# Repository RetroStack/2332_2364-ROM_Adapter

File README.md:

# 2332/2364 ROM Adapter

This repository provides an adapter for 2332 and 2364 ROMs for vintage computers. With an optional hidden inverter chip on the bottom, all versions of these boards can be emulated. The adapter was designed to have the smallest possible footprint while still using through-hole components for a vintage look. It includes an optional detachable selector board for DIP switches or jumpers. Without the detachable selector board, solder jumpers can be used instead. The provided pads on the bottom allow for synchronized address selection across multiple adapters. The entire project is available under the MIT license.

## Project Details

### Latest Files

In the "Latest" folder, you'll find the most up-to-date design files, including:

- Gerber files suitable for popular online PCB manufacturers like [PCBWay](/Latest/2332_2364_ROM_Adapter_Gerber_PCBWay.zip) and [JLCPCB](/Latest/2332_2364_ROM_Adapter_Gerber_JLCPCB.zip). Most manufacturers should be fine with either.
- A Bill of Materials (BOM) in both [CSV](/Latest/2332_2364_ROM_Adapter_BOM.csv) (with sources) and [PDF](/Latest/2332_2364_ROM_Adapter_BOM.pdf) formats.
- The [full schematics](/Latest/2332_2364_ROM_Adapter_Schematics.pdf) of the adapter.

### Implementation

The adapter has been implemented using KiCAD 7. The KiCAD project files are included in this repository.

### Assembly Instructions

1. Get a straight male pin header with pitch (2.54mm; standard) and break it to a 12-pin length. Do this twice. A machined header is recommended if the adapter will be inserted into a socket. Inserting a square pin in a socket might damage it.
2. Solder the pins in place into the smaller 12-pin lengthwise holes. To align them correctly, you can use another socket or a breadboard. Stick the longer parts into the socket/breadboard and put the PCB on top. Solder first both edges on each. Recheck if they are flush to the header. If not, reheat the corner that needs correction and press down on PCB until flush. Then, solder all other pins.
3. Install the resistor network. One edge has a square around one pin. This should be where pin 1 will be inserted. Pin 1 is identified on the resistor network usually with a dot.
4. Write/burn one of the binaries onto a ROM.
5. (Optional) Solder a socket in place. Similarly to the headers mentioned above, only solder one pin on each side before soldering all to be able to make adjustments as needed. Adding a socket is not recommended for machines which do not have enough clearance for it (e.g., TRS-80 Model 1). For these, you need to skip this step and solder the ROM directly to the board.
6. Solder the ROM to the board or insert it into the socket. Since the pins are close, this might be tricky.

#### Bank Switching

The adapter allows for bank-switching of various ROMs. Depending on the size of the ROM used, only certain pins may be configurable. For example, a 27256 ROM has 15 address pins. The adapter exposes 13 of these pins to the bottom pins, leaving 2 additional address lines available for bank-switching. A 27512 would then have 3 additional address lines.

**NOTE**: Keep in mind that the bits are active-low. This means that if you want to set a `1` on a specific address, you leave it unbridged. If you want a `0`, you should bridge it. See below for more details on why it was designed this way.

**NOTE**: The board exposes the bits from right to left. If you prefer left to right (e.g., for DIP switches to match labels), you can flip the address bits in the ROM or use the provided "f" versions in the systems ROM repository.

Here are some examples of available bank-switching configurations:

#### No Bank-Switching at all

7. Clip off extension board on perforated line.
8. Use solder bridges on the bottom to pre-select a specific ROM.

#### Jumper Caps

7. Add a 2-row pin straight header (2.54mm pitch) to the center two pins of the extension board. Make sure to leave one row of pins on each side—one row on the edge and one next to the ROM.
8. Add jumpers.

#### Right Angle Jumpers

7) Clip off extension board on perforated line.
8) Add a 2 row pin right-angle header (2.54mm pitch) to the bottom of the PCB, extending one end out over the board where the extension was.
9) Add jumpers.

#### DIP Switches

**NOTE**: For the TRS-80 Model 1, use low-profile DIP switches to ensure the adapter fits inside the case.
7) Add a DIP switch to the extension board. The DIP switch should cover all holes from front to back.

#### DIP Switches on extension board

7) Clip off the extension board along the perforated line.
8) Solder up to 6 wires (e.g., ribbon cable) to the bottom of the PCB. Use up to 3 wires for each address line, which is the row close to the center of the board. To identify the address lines, refer to the label just below the ROM on the top of the adapter PCB. Solder at least one wire to any of the holes closer to the edge of the board—these are ground pins, so any of them can be used.
9) Solder all wires to the extension board using the central two rows of holes. Solder from the bottom, as the DIP switches will be added to the top. Solder the address lines closest to the perforated line where the extension board was attached to the adapter PCB. Solder the ground wires to the other holes in the second row, further from the perforated edge.
10) Add a DIP switch to the extension board. The DIP switch should cover all holes from front to back. You may need to trim the soldered pins of the cable to allow the DIP switches to sit as close to flush as possible.

#### Jumper caps on extension board

7) Clip off the extension board along the perforated line.  
8) Solder up to 6 wires (e.g., ribbon cable) to the bottom of the PCB. Use up to 3 wires for each address line, which is the row close to the center of the board. To identify which address line is which, refer to the label just below the ROM on the top of the adapter PCB. Solder at least one wire to any of the holes closer to the edge of the board—these are ground pins, so any of them can be used.  
9) Add a 2-row pin straight header (2.54mm pitch) to the center two pins of the extension board. Leave one row on each side—one on the edge and one next to the ROM.  
10) Solder all wires to the extension board. Solder the address lines to the row closer to the perforated edge, and solder the single ground wire to the hole at the bottom edge furthest from the perforated edge. You can solder this from either the top or bottom.  
11) Add jumpers.

#### Connect two or more adapters together

Sometimes it is useful to be able to bank-switch multiple ROMs simultaneously.

7) Clip off the extension boards on nearly all the boards at the perforated line—except one, which will be used for selection.  
8) Solder up to 6 wires (e.g., ribbon cable) to the bottom of one PCB. Use up to 3 wires for each address line, which is the row close to the center of the board. To identify which address line is which, refer to the label just below the ROM on the top of the adapter PCB. Solder at least one wire to any of the holes closer to the edge of the board—these are ground pins, so any of them can be used.  
9) Repeat the same process for the other board using the other end of the wires. Ensure that the wires from each pad on one adapter connect to the corresponding pad on the other adapter.

### Configuration

Depending on which ROM and even the specific version you want to emulate, you will need to configure the adapter accordingly. Below is a list of configurations:

#### 2332 (with pin 20 as "active low")
- Switch jumper JP4: 1) Cut one side, 2) solder the other
- Connect JP8 to either 5V or GND, depending on the value you want for address line A12 (starting from A0).
- Cut jumper JP6

#### 2332 (with pin 20 as "active high")
- Install U3 (74LS04)
- Switch jumper JP7: 1) Cut one side, 2) solder the other

#### 2332 (with pin 21 as "active low")
- This is the default. Nothing else to do.

#### 2332 (with pin 21 as "active high")
- Install U3 (74LS04)
- Switch jumper JP5: 1) Cut one side, 2) solder the other

#### 2364 (with pin 20 as "active low")

This is the default configuration. No additional steps are required.

#### 2364 (with pin 20 as "active high")
- Install U3 (74LS04)
- Switch jumper JP7: 1) Cut one side, 2) solder the other

### Q&A

#### Why is the configuration active low?

Some ROMs, especially EEPROMs, have an active-low WRITE pin that needs to be HIGH (or `1`) during normal (read) use. To prevent accidentally putting ROMs into the incorrect mode (write mode instead of read mode), all additional pins are pulled high by default through pull-up resistors.

#### Why are address lines from right to left?

Having them in this orientation was the simplest solution without adding complexity to the design. Additionally, the addressing depends on the type of configuration you use. Binary numbers are typically written from right to left (as implemented), which works best for jumpers, for example. However, DIP switches use labels from left to right.

Overall, one direction had to be chosen, and I opted for the simplest. This can be adjusted by flipping the address bits. ROMs with this fix are already marked with an "f".

### Bill of Materials (BOM)

Below is a list of materials needed to assemble a complete system. Please note that the links and prices (scroll to the right to see them; as of August 22nd, 2024) will not be updated in the future and should only be used as a reference for locating the correct items.

**NOTE**: Links and alternatives are provided to assist you in finding the necessary components. I cannot guarantee the complete accuracy or reliability of all these links and alternatives. Please verify the information for yourself.

| PCB REFERENCE | QTY | VALUE       | COMMENT                                                                                                                                                                                                                          | EACH | TOTAL | SOURCE LINK                                                                               |
| ------------- | --- | ----------- | -------------------------------------------------------------------------------------------------------------------------------------------------------------------------------------------------------------------------------- | ---- | ----- | ----------------------------------------------------------------------------------------- |
| RN1           | 1   | 4.7k Ohm    | 3 resistor network with 4-pins, bussed resistors                                                                                                                                                                                 | 0.35  | 0.35   | [Mouser](https://www.mouser.com/ProductDetail/652-4604X-1LF-4.7K)                         |
| U1            | 2   |             | Source Link is for a rather expensive version of a machined straight male pin header with 40-pins which can be broken into smaller pieces to server for both. There are cheaper ones, but the link is used for future reference. | 1.0  | 1.0   | [Mouser](https://www.amazon.com/ZYAMY-2-54mm-Breakable-Straight-Connector/dp/B0778KCHHR/) |
| U2            | 1   | 2x64-2x512  | Examples are 23128, 23256, 2764, 27128, 27256, 27512, 2864, 28256 and all other variations such as 27C256 or AT28C64B                                                                                                            | 5.5  | 5.5   | [Mouser](https://www.mouser.com/ProductDetail/556-AT28C64B15PU)                           |
| U3            | 1   | 74LS04  | Optional. Needed for inverting chip select pins. | 0.68  | 0.68   | [Mouser](https://www.mouser.com/ProductDetail/595-SN74LS04D)                           |
| J1            | 1   | -           | Optional. Could be used for right-angle jumpers or attaching ribbon cable to move switch towards more accessible place.                                                                                                          | 1.02 | 1.02  | [Mouser](https://www.mouser.com/ProductDetail/649-1012938294001BLF)                       |
| J2            | 1   | -           | Optional. Adding the ability to switch character sets.                                                                                                                                                                           | 0.27 | 0.27  | [Mouser](https://www.mouser.com/ProductDetail/571-1033222)                                |
|               | 1   | Low-profile | Optional. Adding the ability to switch character sets.                                                                                                                                                                           | 0.67 | 0.67  | [Mouser](https://www.mouser.com/ProductDetail/774-2105MS)                                 |

### ROM Binaries

This repository contains only the adapter boards. The ROM binaries themselves can be found in other repositories and sources. Below is a list of known binary sources:

- [TRS-80 Model 1](https://github.com/RetroStack/TRS-80-Model-I-System-ROMs) - RetroStack

More sources will be added over time. Let me know if you are aware of good sources.

### RetroStack Libraries

To work with this KiCAD project, you'll need the RetroStack libraries for KiCAD. Please [follow this link](https://www.github.com/RetroStack/KiCAD-Libraries) to access and install these libraries.

## Support this Project

RetroStack is passionate about exploring and preserving the legacy of older computer systems. My work involves creating detailed documentation and videos to share the knowledge. I am also dedicated to reviving these classic systems by reimplementing them and offering replacement parts at no cost. If you're keen on supporting this unique project, I invite you to visit my [Patreon page](https://www.patreon.com/RetroStack). Your support would be immensely valuable and greatly appreciated!

## License

This project is licensed under the MIT License - see the [LICENSE](LICENSE) file for details.

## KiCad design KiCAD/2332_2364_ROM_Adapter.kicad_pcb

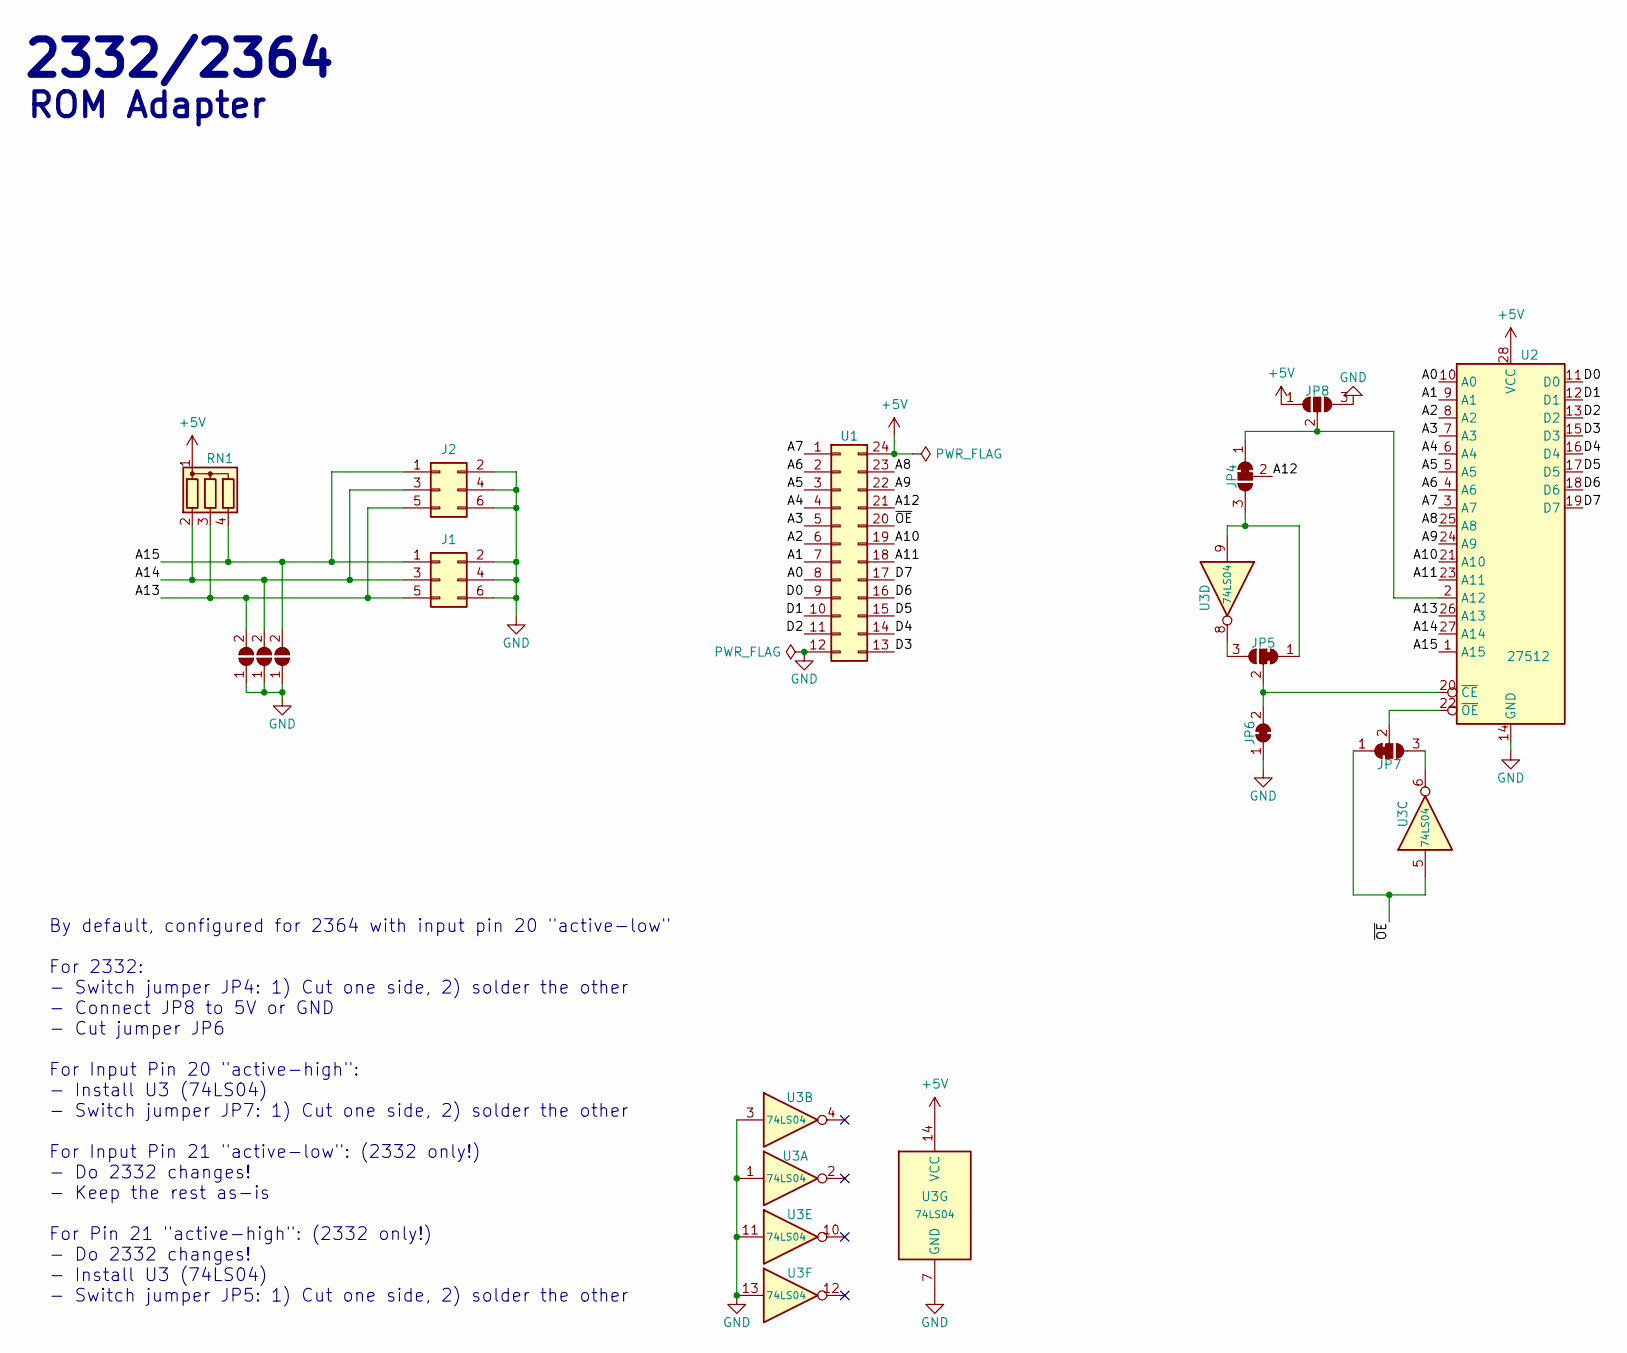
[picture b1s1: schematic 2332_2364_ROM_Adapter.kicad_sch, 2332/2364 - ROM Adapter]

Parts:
J1: Conn_02x03_Odd_Even; DIPJumper_3
J2: Conn_02x03_Odd_Even; PinHeader_2x03_P2.54mm_Vertical
JP1, JP2, JP3: SolderJumper_2_Open; SolderJumper_2_Open_RoundedPad
JP4, JP5, JP7: Switch for 2332!; SolderJumper-3_P1.3mm_Bridged12_RoundedPad1.0x1.5mm_NumberL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
JP6: SolderJumper_2_Bridged; SolderJumper-2_P1.3mm_Bridged_RoundedPad1.0x1.5mm
JP8: SolderJumper_3_Open; SolderJumper-3_P1.3mm_Open_RoundedPad1.0x1.5mm_NumberLabels
RN1: R_Network03; R_Array_SIP4
U1: Conn_02x12_Counter_Clockwise; DIP-24_W15.24mm
U2: 27512; DIP-28_W15.24mm
U3: 74LS04; SOIC-14_3.9x8.7mm_P1.27mm

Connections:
+5V: JP8.1 (A), RN1.1 (common), U1.24, U2.28 (VCC), U3.14 (VCC)
/A0: U1.8, U2.10 (A0)
/A1: U1.7, U2.9 (A1)
/A2: U1.6, U2.8 (A2)
/A3: U1.5, U2.7 (A3)
/A4: U1.4, U2.6 (A4)
/A5: U1.3, U2.5 (A5)
/A6: U1.2, U2.4 (A6)
/A7: U1.1, U2.3 (A7)
/A8: U1.23, U2.25 (A8)
/A9: U1.22, U2.24 (A9)
/A10: U1.19, U2.21 (A10)
/A11: U1.18, U2.23 (A11)
/A12: JP4.2 (C), U1.21
/A13: J1.5, J2.5, JP1.2 (B), RN1.3 (R2), U2.26 (A13)
/A14: J1.3, J2.3, JP2.2 (B), RN1.2 (R1), U2.27 (A14)
/A15: J1.1, J2.1, JP3.2 (B), RN1.4 (R3), U2.1 (A15)
/D0: U1.9, U2.11 (D0)
/D1: U1.10, U2.12 (D1)
/D2: U1.11, U2.13 (D2)
/D3: U1.13, U2.15 (D3)
/D4: U1.14, U2.16 (D4)
/D5: U1.15, U2.17 (D5)
/D6: U1.16, U2.18 (D6)
/D7: U1.17, U2.19 (D7)
/~OE: JP7.1 (A), U1.20, U3.5
GND: J1.2, J1.4, J1.6, J2.2, J2.4, J2.6, JP1.1 (A), JP2.1 (A), JP3.1 (A), JP6.1 (A), JP8.3 (B), U1.12, U2.14 (GND), U3.1, U3.3, U3.7 (GND), U3.11, U3.13
unnamed: JP4.1 (A), JP8.2 (C), U2.2 (A12)
unnamed: JP4.3 (B), JP5.1 (A), U3.9
unnamed: JP5.3 (B), U3.8
unnamed: JP5.2 (C), JP6.2 (B), U2.20 (~CE)
unnamed: JP7.3 (B), U3.6
unnamed: JP7.2 (C), U2.22 (~OE)

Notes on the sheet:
2332/2364
ROM Adapter
By default, configured for 2364 with input pin 20 "active-low" For 2332: - Switch jumper JP4: 1) Cut one side, 2) solder the other - Connect JP8 to 5V or GND - Cut jumper JP6 For Input Pin 20 "active-high": - Install U3 (74LS04) - Switch jumper JP7: 1) Cut one side, 2) solder the other For Input Pi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

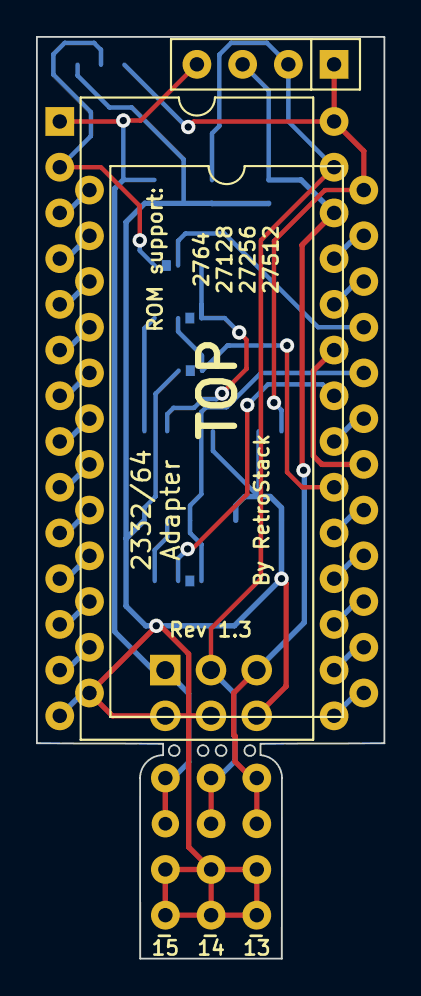
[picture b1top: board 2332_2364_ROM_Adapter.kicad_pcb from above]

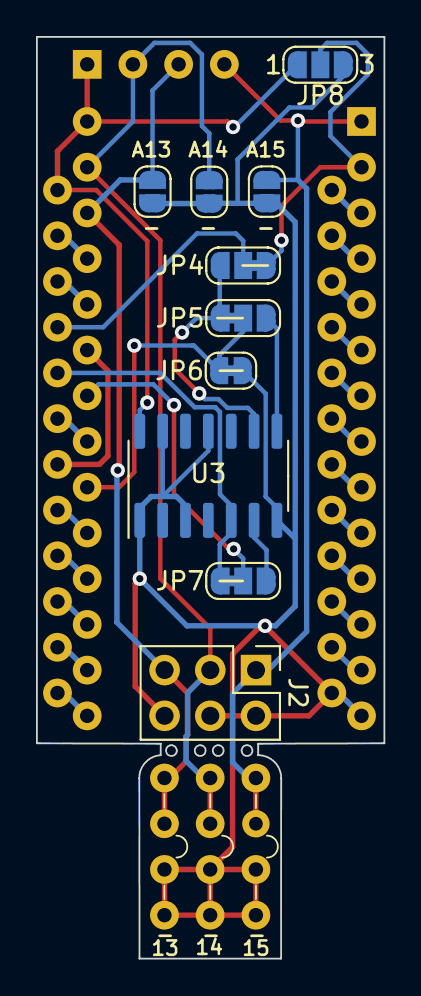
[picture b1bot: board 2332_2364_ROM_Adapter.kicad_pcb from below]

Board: 2 copper layers, 19.3 x 51.2 mm, 14 parts (11 on the bottom side), 33 nets.

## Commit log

2024-08-23 Add photos
2024-08-23 Smaller photos
2024-08-23 Add Schematic image
